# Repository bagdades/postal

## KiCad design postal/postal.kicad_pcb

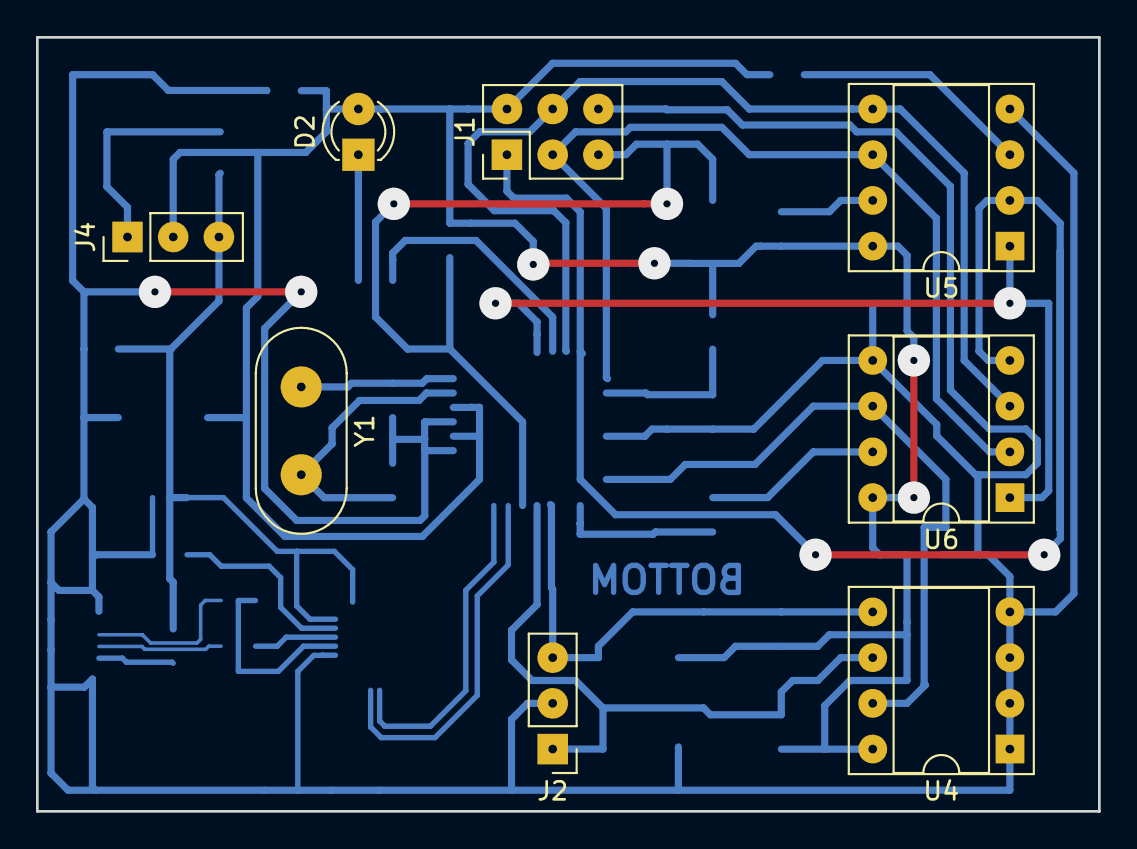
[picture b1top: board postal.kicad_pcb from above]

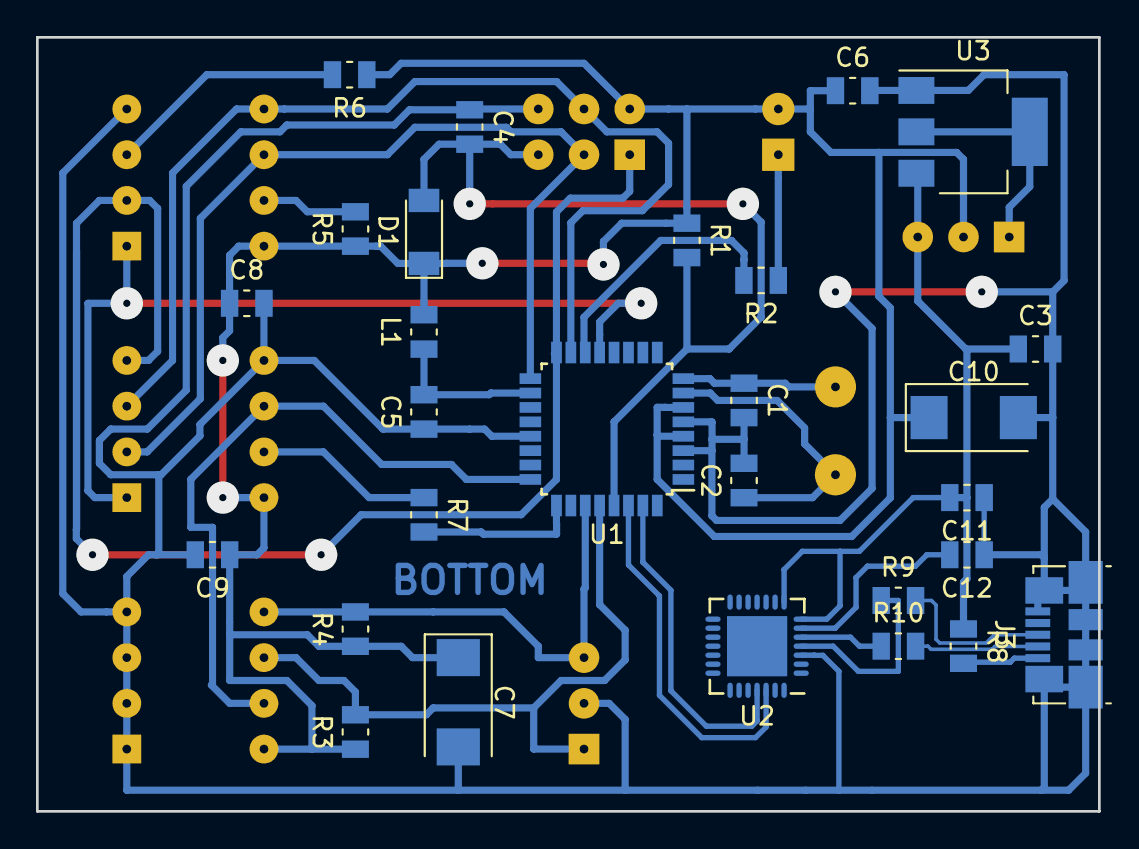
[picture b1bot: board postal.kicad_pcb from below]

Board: 2 copper layers, 59.0 x 43.0 mm, 36 parts (28 on the bottom side), 29 nets.

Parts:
C1, C2: 22p; C_0805_2012Metric
C3, C4, C5, C6, C8, C9, C11, C12: 100n; C_0805_2012Metric
C7, C10: 10u; CP_EIA-6032-28_Kemet-C
D1: D; D_MiniMELF
D2: LED; LED_D3.0mm
J1: SPI_FLASH; PinHeader_2x03_P2.54mm_Vertical
J2: i2c-header; PinHeader_1x03_P2.54mm_Vertical
J3: USB_B_Micro; USB_Micro-B_Molex_47346-0001
J4: PWR; PinHeader_1x03_P2.54mm_Vertical
L1: 10u; L_0805_2012Metric
R1: 4k7; R_0805_2012Metric
R2: 1k5; R_0805_2012Metric
R3, R4: 3k9; R_0805_2012Metric
R5, R6: 10k; R_0805_2012Metric
R7: 1k; R_0805_2012Metric
R8: 0; R_0805_2012Metric
R9, R10: 30; R_0805_2012Metric
U1: ATMEGA8-16AU; LQFP-32_7x7mm_P0.8mm
U2: CP2102; QFN-28-1EP_5x5mm_P0.5mm
U3: AP1117-33; SOT-223-3_TabPin2
U4: 24cXX; DIP-8_W7.62mm_Socket
U5: SPI_FLASH; DIP-8_W7.62mm_Socket
U6: 93CxxA; DIP-8_W7.62mm_Socket
Y1: 14,7456; Crystal_HC49-4H_Vertical

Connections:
/MISO: J1.1, U1.16, U5.2, U6.4
/MOSI: J1.4, U1.15, U5.5, U6.3
/RES: C4.2, D1.2, J1.5, R1.2, U1.29
/RX: U1.30, U2.26
/SCK: J1.3, U1.17, U5.6, U6.2
/SCL: J2.1, R3.2, U1.28, U4.6
/SDA: J2.3, R4.2, U1.27, U4.5
/TX: U1.31, U2.25
GND: C1.2, C2.2, C3.2, C4.1, C5.1, C6.2, C7.2, C8.2, C9.2, C10.2, C11.1, C12.1, J1.6, J2.2, J3.5, J3.6, U1.3, U1.5, U1.21, U2.3, U3.1, U4.1, U4.2, U4.3, U4.4, U5.4, U6.5
unnamed: C1.1, U1.8, Y1.1
unnamed: C2.1, U1.7, Y1.2
unnamed: C5.2, L1.1, U1.18
unnamed: C3.1, C11.2, J4.3, R8.1, U2.7, U2.8, U3.3
unnamed: C12.2, U2.6
unnamed: D2.1, R2.1
unnamed: J3.1, R8.2
unnamed: J3.2, R10.2
unnamed: J3.3, R9.2
unnamed: J4.1, U3.2
unnamed: R2.2, U1.14
unnamed: R5.2, U5.7
unnamed: R6.2, U5.3
unnamed: R7.1, U6.7
unnamed: R7.2, U1.25
unnamed: R9.1, U2.4
unnamed: R10.1, U2.5
unnamed: U1.13, U5.1, U6.1
unnamed: U1.24, U4.7, U6.6
VCC: C6.1, C7.1, C8.1, C9.1, C10.1, D1.1, D2.2, J1.2, J4.2, L1.2, R1.1, R3.1, R4.1, R5.1, R6.1, U1.4, U1.6, U4.8, U5.8, U6.8

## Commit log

2018-01-15 Add docs
2018-01-15 Update pcb
2018-01-16 Create pcb
2018-01-18 Final pcb
2018-01-19 Print pcb
2018-01-23 Final
